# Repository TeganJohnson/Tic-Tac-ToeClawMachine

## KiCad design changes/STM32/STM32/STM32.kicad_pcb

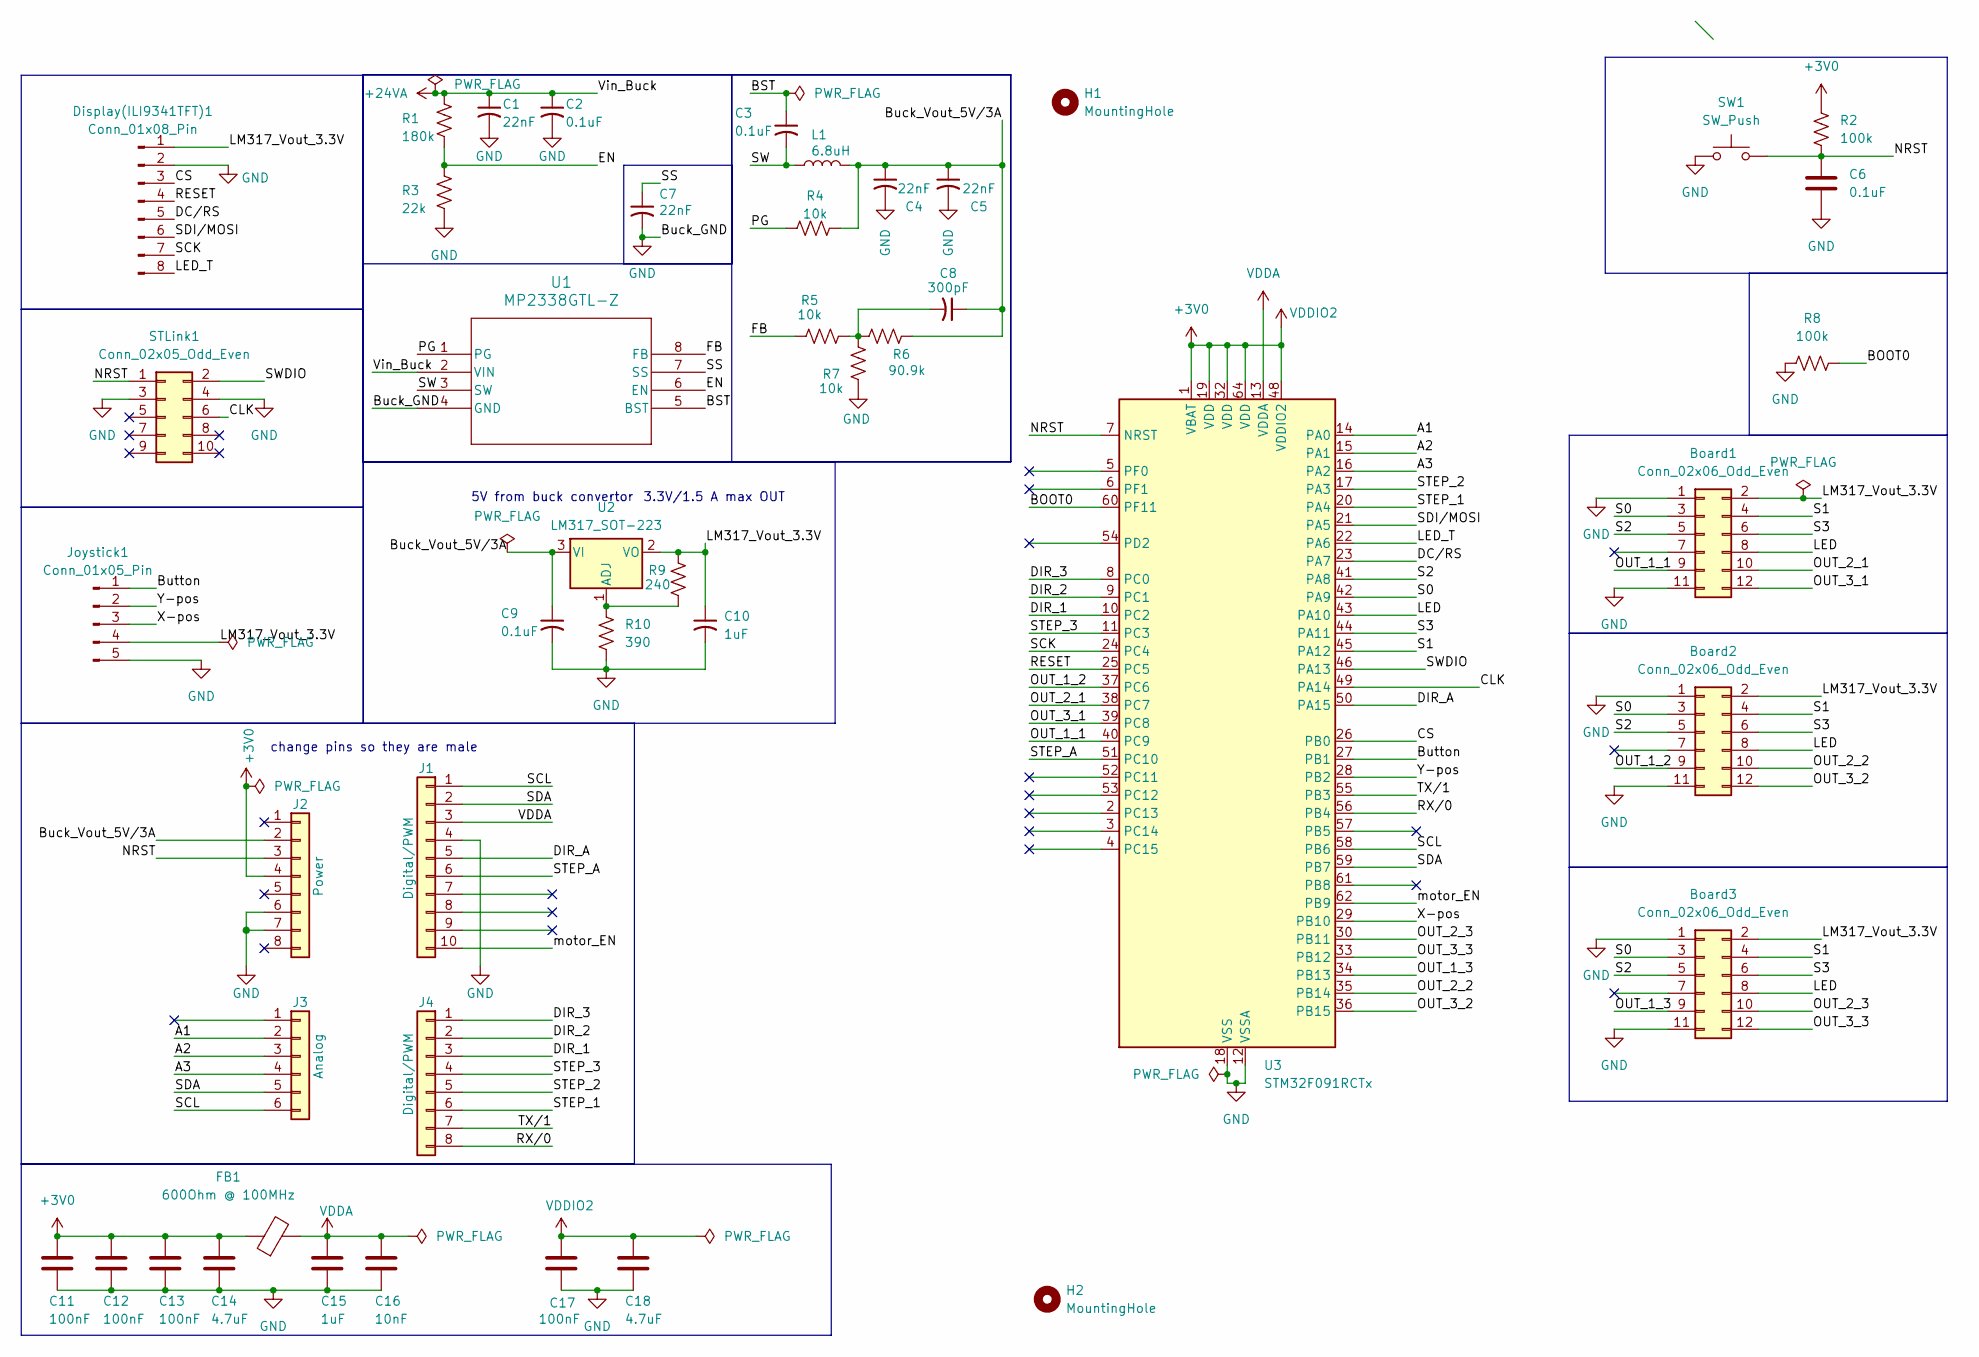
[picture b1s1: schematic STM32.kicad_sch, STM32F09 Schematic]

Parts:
Board1, Board2, Board3: Conn_02x06_Odd_Even; IDC-Header_2x06_P2.54mm_Latch6.5mm_Vertical
C1, C4, C5, C7: 22nF; C_0805_2012Metric
C2, C3, C9: 0.1uF; C_0805_2012Metric
C6: 0.1uF; C_0603_1608Metric
C8: 300pF; C_0805_2012Metric
C10: 1uF; C_0805_2012Metric
C11, C12, C13, C17: 100nF; C_0603_1608Metric
C14, C18: 4.7uF; C_0603_1608Metric
C15: 1uF; C_0603_1608Metric
C16: 10nF; C_0603_1608Metric
Display(ILI9341TFT)1: Conn_01x08_Pin; PinHeader_1x08_P2.54mm_Vertical
FB1: 600Ohm @ 100MHz; R_0603_1608Metric
H1, H2: MountingHole; MountingHole_3.2mm_M3
J1: Digital/PWM; PinSocket_1x10_P2.54mm_Vertical
J2: Power; PinSocket_1x08_P2.54mm_Vertical
J3: Analog; PinSocket_1x06_P2.54mm_Vertical
J4: Digital/PWM; PinSocket_1x08_P2.54mm_Vertical
Joystick1: Conn_01x05_Pin; PinHeader_1x05_P2.54mm_Vertical
L1: 6.8uH; L_0805_2012Metric
R1: 180k; R_0805_2012Metric
R2, R8: 100k; R_0603_1608Metric
R3: 22k; R_0805_2012Metric
R4, R5, R7: 10k; R_0805_2012Metric
R6: 90.9k; R_0805_2012Metric
R9: 240; R_0805_2012Metric
R10: 390; R_0805_2012Metric
STLink1: Conn_02x05_Odd_Even; IDC-Header_2x05_P2.54mm_Vertical
SW1: SW_Push; SW_SPST_TL3342
U1: MP2338GTL-Z; SOT583_MP2338_MNP
U2: LM317_SOT-223; SOT-223-3_TabPin2
U3: STM32F091RCTx; LQFP-64_10x10mm_P0.5mm

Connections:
+3V0: C11.1, C12.1, C13.1, C14.1, C17.1, C18.1, FB1.1, J2.4, R2.1, U3.1 (VBAT), U3.19 (VDD), U3.32 (VDD), U3.48 (VDDIO2), U3.64 (VDD)
+24VA: C1.1, C2.1, R1.1, U1.2 (VIN)
/A1: J3.2, U3.14 (PA0)
/A2: J3.3, U3.15 (PA1)
/A3: J3.4, U3.16 (PA2)
/BOOT0: R8.2, U3.60 (PF11)
/BST: C3.1, U1.5 (BST)
/Buck_Vout_5V/3A: C4.1, C5.1, C8.1, C9.1, J2.2, L1.2, R4.1, R6.2, U2.3 (VI)
/Button: Joystick1.1, U3.27 (PB1)
/CLK: STLink1.6, U3.49 (PA14)
/CS: Display(ILI9341TFT)1.3, U3.26 (PB0)
/DC/RS: Display(ILI9341TFT)1.5, U3.23 (PA7)
/DIR_1: J4.3, U3.10 (PC2)
/DIR_2: J4.2, U3.9 (PC1)
/DIR_3: J4.1, U3.8 (PC0)
/DIR_A: J1.5, U3.50 (PA15)
/EN: R1.2, R3.1, U1.6 (EN)
/FB: R5.2, U1.8 (FB)
/LED: Board1.8, Board2.8, Board3.8, U3.43 (PA10)
/LED_T: Display(ILI9341TFT)1.8, U3.22 (PA6)
/LM317_Vout_3.3V: Board1.2, Board2.2, Board3.2, C10.1, Display(ILI9341TFT)1.1, Joystick1.4, R9.1, U2.2 (VO)
/NRST: C6.1, J2.3, R2.2, STLink1.1, SW1.2, U3.7 (NRST)
/OUT_1_1: Board1.9, U3.40 (PC9)
/OUT_1_2: Board2.9, U3.37 (PC6)
/OUT_1_3: Board3.9, U3.34 (PB13)
/OUT_2_1: Board1.10, U3.38 (PC7)
/OUT_2_2: Board2.10, U3.35 (PB14)
/OUT_2_3: Board3.10, U3.30 (PB11)
/OUT_3_1: Board1.12, U3.39 (PC8)
/OUT_3_2: Board2.12, U3.36 (PB15)
/OUT_3_3: Board3.12, U3.33 (PB12)
/PG: R4.2, U1.1 (PG)
/RESET: Display(ILI9341TFT)1.4, U3.25 (PC5)
/RX/0: J4.8, U3.56 (PB4)
/S0: Board1.3, Board2.3, Board3.3, U3.42 (PA9)
/S1: Board1.4, Board2.4, Board3.4, U3.45 (PA12)
/S2: Board1.5, Board2.5, Board3.5, U3.41 (PA8)
/S3: Board1.6, Board2.6, Board3.6, U3.44 (PA11)
/SCK: Display(ILI9341TFT)1.7, U3.24 (PC4)
/SCL: J1.1, J3.6, U3.58 (PB6)
/SDA: J1.2, J3.5, U3.59 (PB7)
/SDI/MOSI: Display(ILI9341TFT)1.6, U3.21 (PA5)
/SS: C7.1, U1.7 (SS)
/STEP_1: J4.6, U3.20 (PA4)
/STEP_2: J4.5, U3.17 (PA3)
/STEP_3: J4.4, U3.11 (PC3)
/STEP_A: J1.6, U3.51 (PC10)
/SW: C3.2, L1.1, U1.3 (SW)
/SWDIO: STLink1.2, U3.46 (PA13)
/TX/1: J4.7, U3.55 (PB3)
/X-pos: Joystick1.3, U3.29 (PB10)
/Y-pos: Joystick1.2, U3.28 (PB2)
/motor_EN: J1.10, U3.62 (PB9)
GND: Board1.1, Board1.11, Board2.1, Board2.11, Board3.1, Board3.11, C1.2, C2.2, C4.2, C5.2, C6.2, C7.2, C9.2, C10.2, C11.2, C12.2, C13.2, C14.2, C15.2, C16.2, C17.2, C18.2, Display(ILI9341TFT)1.2, J1.4, J2.6, J2.7, Joystick1.5, R3.2, R7.2, R8.1, R10.2, STLink1.3, STLink1.4, SW1.1, U1.4 (GND), U3.12 (VSSA), U3.18 (VSS), U3.31 (VSS), U3.47 (VSS), U3.63 (VSS)
unnamed: C8.2, R5.1, R6.1, R7.1
unnamed: R9.2, R10.1, U2.1 (ADJ)
VDDA: C15.1, C16.1, FB1.2, J1.3, U3.13 (VDDA)

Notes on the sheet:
3.3V/1.5 A max OUT
change pins so they are male
5V from buck convertor

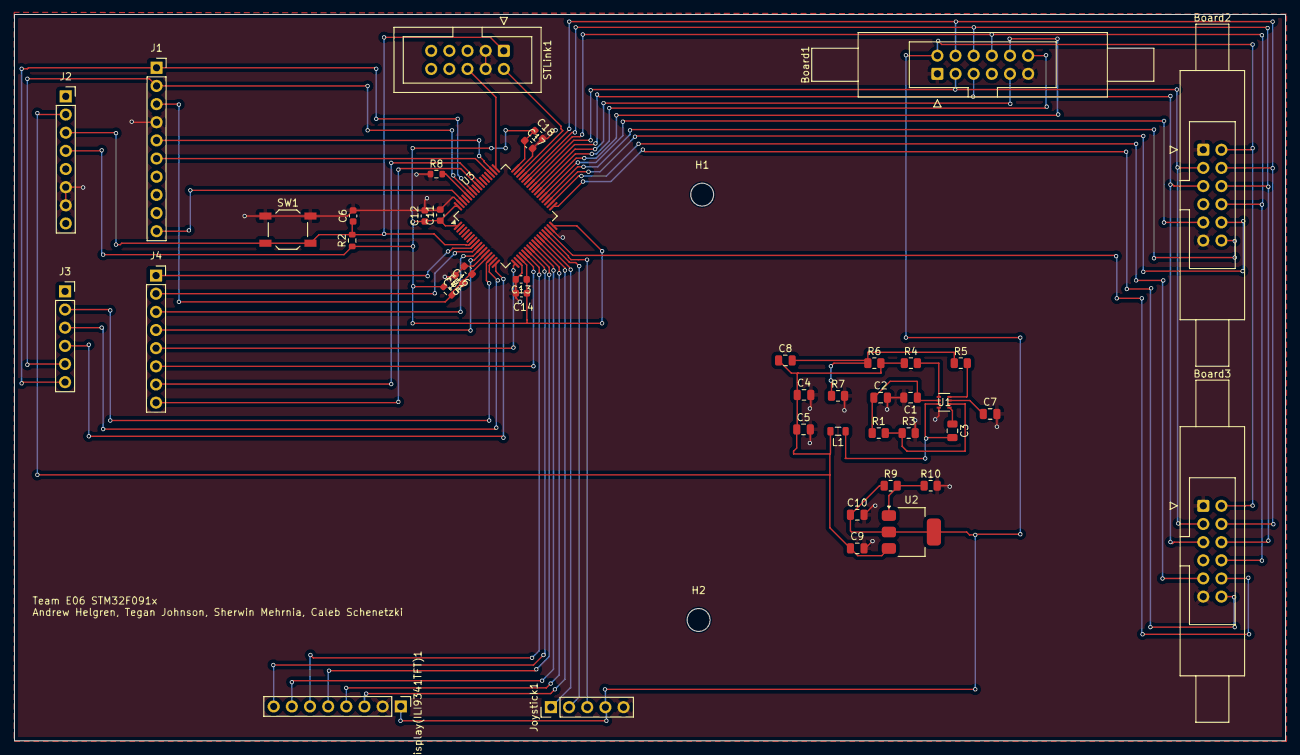
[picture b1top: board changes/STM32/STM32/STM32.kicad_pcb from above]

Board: 2 copper layers, 177.8 x 101.6 mm, 46 parts (0 on the bottom side), 57 nets.

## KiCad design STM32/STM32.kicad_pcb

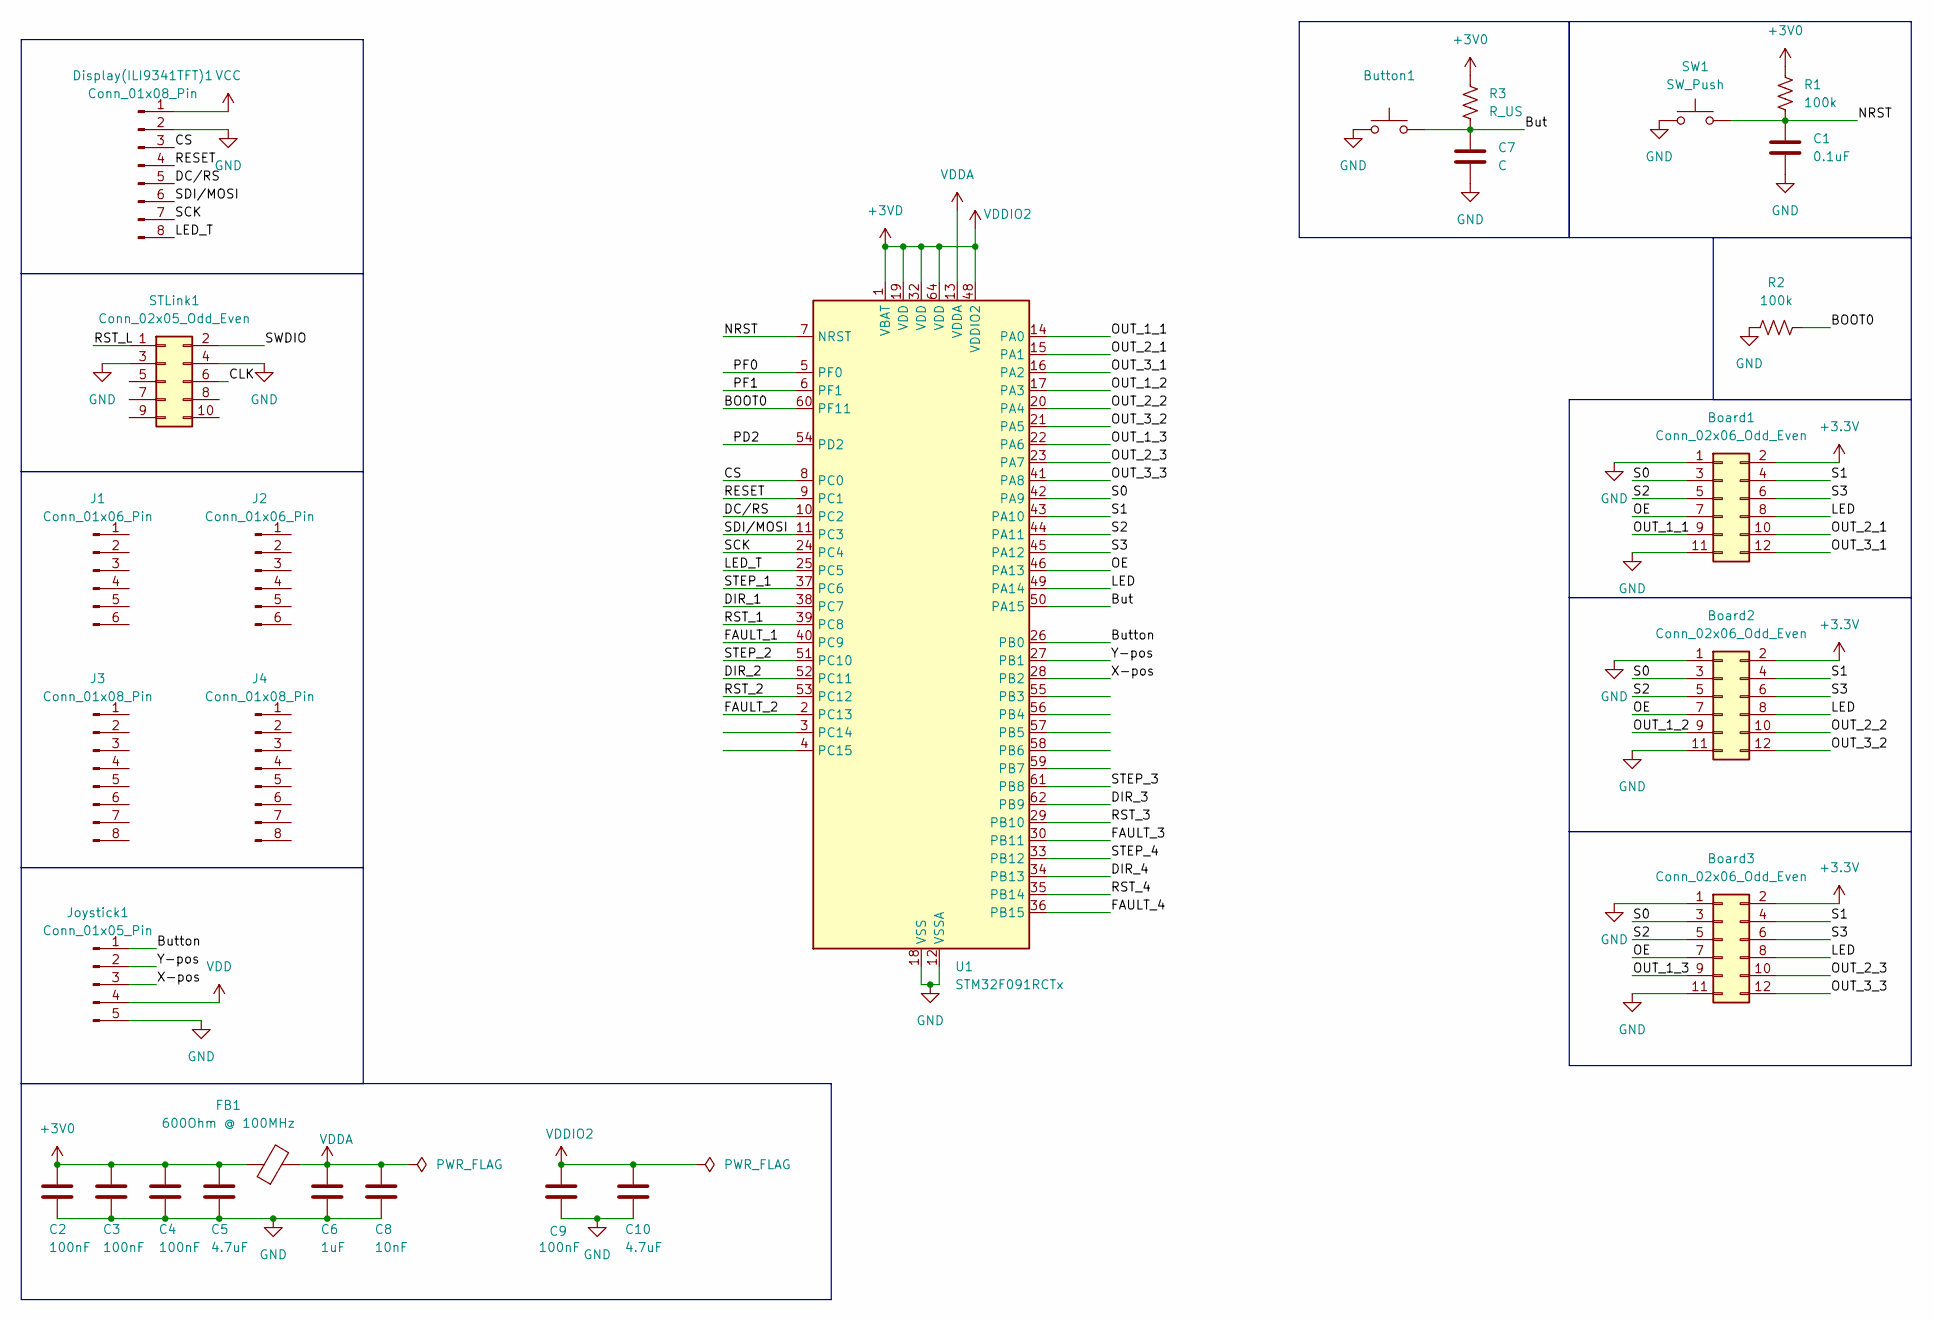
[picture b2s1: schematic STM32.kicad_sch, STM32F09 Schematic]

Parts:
Board1, Board2, Board3: Conn_02x06_Odd_Even; PinHeader_2x06_P1.00mm_Vertical
Button1: SW_SPST_TL3342
C1: 0.1uF; C_0603_1608Metric
C2, C3, C4, C9: 100nF; C_0603_1608Metric
C5, C10: 4.7uF; C_0603_1608Metric
C6: 1uF; C_0603_1608Metric
C7: C; C_0603_1608Metric
C8: 10nF; C_0603_1608Metric
Display(ILI9341TFT)1: Conn_01x08_Pin; PinHeader_1x08_P1.00mm_Vertical
FB1: 600Ohm @ 100MHz; R_0603_1608Metric
J1, J2: Conn_01x06_Pin; PinHeader_1x06_P1.00mm_Vertical
J3, J4: Conn_01x08_Pin; PinHeader_1x08_P1.00mm_Vertical
Joystick1: Conn_01x05_Pin; PinHeader_1x05_P1.00mm_Vertical
R1, R2: 100k; R_0603_1608Metric
R3: R_US; R_0603_1608Metric
STLink1: Conn_02x05_Odd_Even; PinHeader_2x05_P1.00mm_Vertical
SW1: SW_Push; SW_SPST_TL3342
U1: STM32F091RCTx; LQFP-64_10x10mm_P0.5mm

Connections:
+3.3V: Board1.2, Board2.2, Board3.2
+3V0: C2.1, C3.1, C4.1, C5.1, FB1.1, R1.1, R3.1
+3VD: C9.1, C10.1, U1.1 (VBAT), U1.19 (VDD), U1.32 (VDD), U1.48 (VDDIO2), U1.64 (VDD)
/BOOT0: R2.2, U1.60 (PF11)
/But: Button1.2, C7.1, R3.2, U1.50 (PA15)
/Button: Joystick1.1, U1.26 (PB0)
/CLK: STLink1.6
/CS: Display(ILI9341TFT)1.3, U1.8 (PC0)
/DC/RS: Display(ILI9341TFT)1.5, U1.10 (PC2)
/DIR_1: U1.38 (PC7)
/DIR_2: U1.52 (PC11)
/DIR_3: U1.62 (PB9)
/DIR_4: U1.34 (PB13)
/FAULT_1: U1.40 (PC9)
/FAULT_2: U1.2 (PC13)
/FAULT_3: U1.30 (PB11)
/FAULT_4: U1.36 (PB15)
/LED: Board1.8, Board2.8, Board3.8, U1.49 (PA14)
/LED_T: Display(ILI9341TFT)1.8, U1.25 (PC5)
/NRST: C1.1, R1.2, SW1.2, U1.7 (NRST)
/OE: Board1.7, Board2.7, Board3.7, U1.46 (PA13)
/OUT_1_1: Board1.9, U1.14 (PA0)
/OUT_1_2: Board2.9, U1.17 (PA3)
/OUT_1_3: Board3.9, U1.22 (PA6)
/OUT_2_1: Board1.10, U1.15 (PA1)
/OUT_2_2: Board2.10, U1.20 (PA4)
/OUT_2_3: Board3.10, U1.23 (PA7)
/OUT_3_1: Board1.12, U1.16 (PA2)
/OUT_3_2: Board2.12, U1.21 (PA5)
/OUT_3_3: Board3.12, U1.41 (PA8)
/PD2: U1.54 (PD2)
/PF0: U1.5 (PF0)
/PF1: U1.6 (PF1)
/RESET: Display(ILI9341TFT)1.4, U1.9 (PC1)
/RST_1: U1.39 (PC8)
/RST_2: U1.53 (PC12)
/RST_3: U1.29 (PB10)
/RST_4: U1.35 (PB14)
/RST_L: STLink1.1
/S0: Board1.3, Board2.3, Board3.3, U1.42 (PA9)
/S1: Board1.4, Board2.4, Board3.4, U1.43 (PA10)
/S2: Board1.5, Board2.5, Board3.5, U1.44 (PA11)
/S3: Board1.6, Board2.6, Board3.6, U1.45 (PA12)
/SCK: Display(ILI9341TFT)1.7, U1.24 (PC4)
/SDI/MOSI: Display(ILI9341TFT)1.6, U1.11 (PC3)
/STEP_1: U1.37 (PC6)
/STEP_2: U1.51 (PC10)
/STEP_3: U1.61 (PB8)
/STEP_4: U1.33 (PB12)
/SWDIO: STLink1.2
/X-pos: Joystick1.3, U1.28 (PB2)
/Y-pos: Joystick1.2, U1.27 (PB1)
GND: Board1.1, Board1.11, Board2.1, Board2.11, Board3.1, Board3.11, Button1.1, C1.2, C2.2, C3.2, C4.2, C5.2, C6.2, C7.2, C8.2, C9.2, C10.2, Display(ILI9341TFT)1.2, Joystick1.5, R2.1, STLink1.3, STLink1.4, SW1.1, U1.12 (VSSA), U1.18 (VSS), U1.31 (VSS), U1.47 (VSS), U1.63 (VSS)
VCC: Display(ILI9341TFT)1.1
VDD: Joystick1.4
VDDA: C6.1, C8.1, FB1.2, U1.13 (VDDA)

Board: 2 copper layers, 27 parts (0 on the bottom side), 32 nets, no tracks yet.

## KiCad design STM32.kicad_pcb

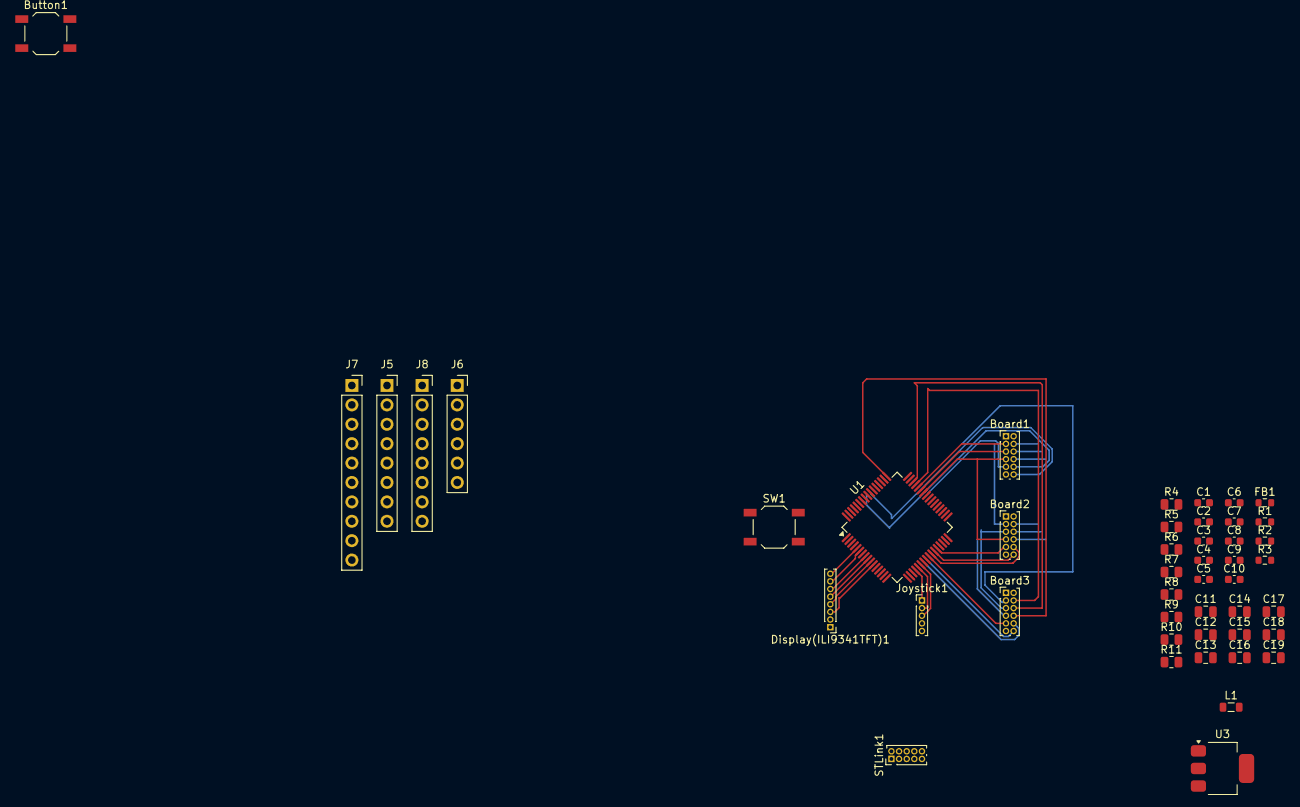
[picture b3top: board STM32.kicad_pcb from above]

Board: 2 copper layers, 46 parts (0 on the bottom side), 42 nets.

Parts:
Board1, Board2, Board3: Conn_02x06_Odd_Even; PinHeader_2x06_P1.00mm_Vertical
Button1: SW_SPST_TL3342
C1: 0.1uF; C_0603_1608Metric
C2, C3, C4, C9: 100nF; C_0603_1608Metric
C5, C10: 4.7uF; C_0603_1608Metric
C6: 1uF; C_0603_1608Metric
C7: C; C_0603_1608Metric
C8: 10nF; C_0603_1608Metric
C11, C14, C15, C16: 22nF; C_0805_2012Metric
C12, C13, C18: 0.1uF; C_0805_2012Metric
C17: 300pF; C_0805_2012Metric
C19: 1uF; C_0805_2012Metric
Display(ILI9341TFT)1: Conn_01x08_Pin; PinHeader_1x08_P1.00mm_Vertical
FB1: 600Ohm @ 100MHz; R_0603_1608Metric
J5: Power; PinSocket_1x08_P2.54mm_Vertical
J6: Analog; PinSocket_1x06_P2.54mm_Vertical
J7: Digital/PWM; PinSocket_1x10_P2.54mm_Vertical
J8: Digital/PWM; PinSocket_1x08_P2.54mm_Vertical
Joystick1: Conn_01x05_Pin; PinHeader_1x05_P1.00mm_Vertical
L1: 6.8uH; L_0805_2012Metric
R1, R2: 100k; R_0603_1608Metric
R3: R_US; R_0603_1608Metric
R4: 180k; R_0805_2012Metric
R5: 22k; R_0805_2012Metric
R6, R7, R9: 10k; R_0805_2012Metric
R8: 90.9k; R_0805_2012Metric
R10: 240; R_0805_2012Metric
R11: 390; R_0805_2012Metric
STLink1: Conn_02x05_Odd_Even; PinHeader_2x05_P1.00mm_Vertical
SW1: SW_Push; SW_SPST_TL3342
U1: STM32F091RCTx; LQFP-64_10x10mm_P0.5mm
U3: LM317_SOT-223; SOT-223-3_TabPin2

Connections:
+3.3V: Board1.2, Board2.2, Board3.2
+3V0: C2.1, C3.1, C4.1, C5.1, C9.1, C10.1, FB1.1, R1.1, R3.1, U1.1 (VBAT), U1.19 (VDD), U1.32 (VDD), U1.48 (VDDIO2), U1.64 (VDD)
+5V: C18.1, J5.5, U3.3 (VI)
+24VA: C11.1, C12.1, R4.1
/BOOT0: R2.2, U1.60 (PF11)
/Buck_Vout_5V/3A: C14.1, C15.1, C17.1, L1.2, R6.1, R8.2
/But: Button1.2, C7.1, R3.2, U1.50 (PA15)
/Button: Joystick1.1, U1.20 (PA4)
/CS: Display(ILI9341TFT)1.3, U1.11 (PC3)
/DC/RS: Display(ILI9341TFT)1.5, U1.9 (PC1)
/EN: R4.2, R5.1
/LED: Board1.8, Board2.8, Board3.8, U1.49 (PA14)
/LED_T: Display(ILI9341TFT)1.8, U1.5 (PF0)
/LM317_Vout_3.3V: C19.1, R10.1, U3.2 (VO)
/NRST: C1.1, R1.2, SW1.2, U1.7 (NRST)
/OE: Board1.7, Board2.7, Board3.7, U1.42 (PA9)
/OUT_1_1: Board1.9, U1.41 (PA8)
/OUT_1_2: Board2.9, U1.28 (PB2)
/OUT_1_3: Board3.9, U1.25 (PC5)
/OUT_2_1: Board1.10, U1.56 (PB4)
/OUT_2_2: Board2.10, U1.26 (PB0)
/OUT_2_3: Board3.10, U1.23 (PA7)
/OUT_3_1: Board1.12, U1.55 (PB3)
/OUT_3_2: Board2.12, U1.27 (PB1)
/OUT_3_3: Board3.12, U1.24 (PC4)
/RESET: Display(ILI9341TFT)1.4, U1.10 (PC2)
/S0: Board1.3, Board2.3, Board3.3, U1.44 (PA11)
/S1: Board1.4, Board2.4, Board3.4, U1.45 (PA12)
/S2: Board1.5, Board2.5, Board3.5, U1.43 (PA10)
/S3: Board1.6, Board2.6, Board3.6, U1.46 (PA13)
/SCK: Display(ILI9341TFT)1.7, U1.6 (PF1)
/SCL/A5: J6.6, J7.1
/SDA/A4: J6.5, J7.2
/SDI/MOSI: Display(ILI9341TFT)1.6, U1.8 (PC0)
/SW: C13.2, L1.1
/X-pos: Joystick1.3, U1.22 (PA6)
/Y-pos: Joystick1.2, U1.21 (PA5)
GND: Board1.1, Board1.11, Board2.1, Board2.11, Board3.1, Board3.11, Button1.1, C1.2, C2.2, C3.2, C4.2, C5.2, C6.2, C7.2, C8.2, C9.2, C10.2, C11.2, C12.2, C14.2, C15.2, C16.2, C18.2, C19.2, Display(ILI9341TFT)1.2, J5.6, J5.7, J7.4, Joystick1.5, R2.1, R5.2, R9.2, R11.2, STLink1.3, STLink1.4, SW1.1, U1.12 (VSSA), U1.18 (VSS), U1.31 (VSS), U1.47 (VSS), U1.63 (VSS)
unnamed: C17.2, R7.1, R8.1, R9.1
unnamed: R10.2, R11.1, U3.1 (ADJ)
VCC: Display(ILI9341TFT)1.1, J5.8
VDDA: C6.1, C8.1, FB1.2, U1.13 (VDDA)

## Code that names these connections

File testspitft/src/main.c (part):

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#include "display.h"

// LCD Pin Connections (STM32F091RC)
// PB0  -> Chip Select (CS)
// PC5  -> Reset (RST)
// PA7  -> Data/Command Select (DC/RS)
// PA6  -> Backlight (LED_T)
// PC4  -> SPI1_SCK  (AF0)
// PA5  -> SPI1_MOSI (AF0)

#define LCD_CS_GPIO GPIOB
#define LCD_CS_PIN 0
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#define JOY_GPIO GPIOB
#define JOY_BTN_PIN 1

#define JOY_X_CHANNEL ADC_CHSELR_CHSEL0 // PB10 -> ADC channel 11 PA0 - 0
#define JOY_Y_CHANNEL ADC_CHSELR_CHSEL1 // PB2  -> ADC channel 12 (if wired, else verify) PA1 - 1

#define X_LIMIT_GPIO GPIOB
#define X_LIMIT_PIN 4
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    // Enable GPIOA, GPIOB, GPIOC clocks
    RCC->AHBENR |= RCC_AHBENR_GPIOAEN | RCC_AHBENR_GPIOBEN | RCC_AHBENR_GPIOCEN;

    // PB0 (CS) output, start high (deselected)
    GPIOB->MODER &= ~(3 << (0 * 2));
    GPIOB->MODER |= (1 << (0 * 2));
    GPIOB->BSRR = (1 << 0);

    // PC5 (RST) output, start high
    GPIOC->MODER &= ~(3 << (5 * 2));
    GPIOC->MODER |= (1 << (5 * 2));
    GPIOC->BSRR = (1 << 5);

    // PA7 (DC) output now pc4
    GPIOC->MODER &= ~(3 << (4 * 2));
    GPIOC->MODER |= (1 << (4 * 2));

    // PA6 (Backlight) output, start high (on)
    GPIOA->MODER &= ~(3 << (6 * 2));
    GPIOA->MODER |= (1 << (6 * 2));
    GPIOA->BSRR = (1 << 6);

    // PC4 -> SPI1_SCK AF0 now pa5
    GPIOA->MODER &= ~(3 << (5 * 2));
    GPIOA->MODER |= (2 << (5 * 2));
    GPIOA->AFR[0] &= ~(0xF << (5 * 4));

    // PA5 -> SPI1_MOSI AF0 mpw pa7
    GPIOA->MODER &= ~(3 << (7 * 2));
    GPIOA->MODER |= (2 << (7 * 2));
    GPIOA->AFR[0] &= ~(0xF << (7 * 4));

    // PB10 (X-pos) analog, ADC ch11 not PA0
    GPIOA->MODER |= (3 << (0 * 2));
    GPIOA->PUPDR &= ~(3 << (0 * 2));

    // PB2 (Y-pos) analog, ADC ch12 now PA1
    GPIOA->MODER |= (3 << (1 * 2));
    GPIOA->PUPDR &= ~(3 << (1 * 2));

    // PB1 (Button) input with pull-up
    GPIOB->MODER &= ~(3 << (JOY_BTN_PIN * 2));
    GPIOB->PUPDR &= ~(3 << (JOY_BTN_PIN * 2));
    GPIOB->PUPDR |= (1 << (JOY_BTN_PIN * 2));

    // --- Shared TCS control pins: PA8, PA9, PA10, PA11, PA12 as outputs ---
    GPIOA->MODER &= ~((3 << (8 * 2)) |
                      (3 << (9 * 2)) |
                      (3 << (10 * 2)) |
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
    // --- 9 TCS output pins as digital inputs ---

    // PC6, PC7, PC8, PC9
    GPIOC->MODER &= ~((3 << (6 * 2)) |
                      (3 << (7 * 2)) |
                      (3 << (8 * 2)) |
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                      (3 << (8 * 2)) |
                      (3 << (9 * 2)));

    // PB11, PB12, PB13, PB14, PB15
    GPIOB->MODER &= ~((3 << (11 * 2)) |
                      (3 << (12 * 2)) |
                      (3 << (13 * 2)) |
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
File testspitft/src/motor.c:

#include "motor.h"
 
// -----------------------------------------------------------------------------
// External timing functions from main.c
// ----------------------------------------------------------------------------
extern uint32_t millis(void);
extern void delay_ms(uint32_t ms);

// -----------------------------------------------------------------------------
// Number of Steps to Lower/Raise to/from the Play Area
// -----------------------------------------------------------------------------
#define LOWER_STEPS 1000
#define RAISE_STEPS 1000

// -----------------------------------------------------------------------------
// Number of Steps to Close/Open the Claw
// -----------------------------------------------------------------------------
#define CLOSE_STEPS 10
#define OPEN_STEPS 10 

// -----------------------------------------------------------------------------
// Number of Steps to Set the Drop Height
// -----------------------------------------------------------------------------
#define DROP_STEPS 0
#define DROP_RAISE_STEPS 0

#define X_LIMIT_GPIO GPIOB
#define X_LIMIT_PIN 3

#define Y_LIMIT_GPIO GPIOB
#define Y_LIMIT_PIN 4

// -----------------------------------------------------------------------------
// Microsecond busy-wait
// Assumes 8MHz system clock. Adjust cycle count if clock changes.
// Each loop iteration ~ 4 cycles at 8MHz = 0.5us, so 2 iterations ~ 1us.
// -----------------------------------------------------------------------------
static void delay_us(uint32_t us)
{
    volatile uint32_t cycles = us * 2;
    while (cycles--) __NOP();
}
 
// -----------------------------------------------------------------------------
// Pin mapping — matches confirmed schematic
// -----------------------------------------------------------------------------
//   AXIS_X    STEP=PA4  DIR=PC2
//   AXIS_Y    STEP=PA3  DIR=PC1
//   AXIS_Z    STEP=PC3  DIR=PC0
//   AXIS_CLAW STEP=PC10 DIR=PA15
//
// Shared enable: PB9 (active LOW on DRV8825)
// -----------------------------------------------------------------------------

#define MOTOR_EN_PORT   GPIOB
#define MOTOR_EN_PIN    9
 
static const motor_pins_t motor_pins[AXIS_COUNT] = {
    [AXIS_X]    = { GPIOA, 4,  GPIOC, 2  },
    [AXIS_Y]    = { GPIOA, 3,  GPIOC, 1  },
    [AXIS_Z]    = { GPIOC, 3,  GPIOC, 0  },
    [AXIS_CLAW] = { GPIOC, 10, GPIOA, 15 },
};

// -----------------------------------------------------------------------------
//A helper function for Motor_Init
// -----------------------------------------------------------------------------
void gpio_pullup(GPIO_TypeDef *port, uint8_t pin) {
    port->MODER &= ~(3 << (pin * 2));
    port->PUPDR &= ~(3 << (pin * 2));
    port->PUPDR |= (1 << (pin * 2));
}

 
// -----------------------------------------------------------------------------
// Motor_Init
// Configures all STEP, DIR, and EN pins as outputs.
// Call after GPIO clocks have been enabled in GPIO_Init().
// -----------------------------------------------------------------------------
void Motor_Init(void)
{

    gpio_pullup(X_LIMIT_GPIO, X_LIMIT_PIN);
    gpio_pullup(Y_LIMIT_GPIO, Y_LIMIT_PIN);

    // Enable pin — PB9 output, start HIGH (disabled)
    MOTOR_EN_PORT->MODER &= ~(3 << (MOTOR_EN_PIN * 2));
    MOTOR_EN_PORT->MODER |=  (1 << (MOTOR_EN_PIN * 2));
    MOTOR_EN_PORT->BSRR   =  (1 << MOTOR_EN_PIN);      // HIGH = disabled
 
    for (uint8_t i = 0; i < AXIS_COUNT; i++) {
        const motor_pins_t *p = &motor_pins[i];
 
        // STEP pin — output, start low
        p->step_port->MODER &= ~(3 << (p->step_pin * 2));
        p->step_port->MODER |=  (1 << (p->step_pin * 2));
        p->step_port->BRR    =  (1 << p->step_pin);
 
        // DIR pin — output, start low
        p->dir_port->MODER &= ~(3 << (p->dir_pin * 2));
        p->dir_port->MODER |=  (1 << (p->dir_pin * 2));
        p->dir_port->BRR    =  (1 << p->dir_pin);
    }
}
 
// -----------------------------------------------------------------------------
// Motor_Enable / Motor_Disable
// DRV8825 EN is active LOW — pull low to enable, high to disable.
// Disable when not moving to reduce heat and current draw.
// -----------------------------------------------------------------------------
void Motor_Enable(void)
{
    MOTOR_EN_PORT->BRR  = (1 << MOTOR_EN_PIN);   // LOW = enabled
}
 
void Motor_Disable(void)
{
    MOTOR_EN_PORT->BSRR = (1 << MOTOR_EN_PIN);   // HIGH = disabled
}
 
//Motor_Step2, currently is blocking.
//takes up to 2 axis and moves them the given number of steps.
//unused axis should be input as 2
void Motor_Step2(axis_t axis1, axis_t axis2, motor_dir_t dir, uint32_t steps)
{
    if (axis1 >= AXIS_COUNT || axis2 >= AXIS_COUNT || steps == 0) return;
 
    const motor_pins_t *p1 = &motor_pins[axis1];

    const motor_pins_t *p2 = &motor_pins[axis2];

    if (dir == DIR_FORWARD) {
    p2->dir_port->BSRR = (1 << p2->dir_pin);   // HIGH
    } else {
    p2->dir_port->BRR  = (1 << p2->dir_pin);   // LOW
    }
        
    if (dir == DIR_FORWARD) {
    p1->dir_port->BSRR = (1 << p1->dir_pin);   // HIGH
    } else {
    p1->dir_port->BRR  = (1 << p1->dir_pin);   // LOW
    }

    //delay for DRV8825 setup
    delay_us(2);
 
    for (uint32_t i = 0; i < steps; i++) {
        // Pulse STEP high
        p1->step_port->BSRR = (1 << p1->step_pin);
        p2->step_port->BSRR = (1 << p2->step_pin);
        delay_us(MOTOR_PULSE_US);
 
        // Pulse STEP low
        p1->step_port->BRR  = (1 << p1->step_pin);

        p2->step_port->BRR  = (1 << p2->step_pin);
        delay_us(MOTOR_STEP_DELAY_US);
    }
    }


void Motor_Step(axis_t axis1, motor_dir_t dir, uint32_t steps)
{
    if (axis1 >= AXIS_COUNT || steps == 0) return;
 
    const motor_pins_t *p = &motor_pins[axis1];
 
    //set direction
    if (dir == DIR_FORWARD) {
        p->dir_port->BSRR = (1 << p->dir_pin);   // HIGH
    } else {
        p->dir_port->BRR  = (1 << p->dir_pin);   // LOW
    }

    //delay for DRV8825 setup
    delay_us(2);
 
    for (uint32_t i = 0; i < steps; i++) {
        // Pulse STEP high
        p->step_port->BSRR = (1 << p->step_pin);
        delay_us(MOTOR_PULSE_US);
 
        // Pulse STEP low
        p->step_port->BRR  = (1 << p->step_pin);
        delay_us(MOTOR_STEP_DELAY_US);
    }
}

void Claw_Grab_Token(void) {
    Motor_MoveZ(DIR_FORWARD, LOWER_STEPS);
    delay_ms(1000);
    Motor_MoveClaw(DIR_FORWARD, CLOSE_STEPS);
    Motor_MoveZ(DIR_BACKWARD, RAISE_STEPS);
}

void Claw_Drop_Token(void) {
    if (DROP_STEPS != 0) {
        Motor_MoveZ(DIR_FORWARD, DROP_STEPS);
    }

    Motor_MoveClaw(DIR_BACKWARD, OPEN_STEPS);

    if (DROP_STEPS != 0) {
        Motor_MoveZ(DIR_FORWARD, DROP_RAISE_STEPS);
    }
}
 
//wrappers
void Motor_MoveX(motor_dir_t dir, uint32_t steps)
{
    Motor_Step(AXIS_X, dir, steps);
}
 
void Motor_MoveY(motor_dir_t dir, uint32_t steps)
{
    Motor_Step(AXIS_Y, dir, steps);
}
 
void Motor_MoveZ(motor_dir_t dir, uint32_t steps)
{
    Motor_Step(AXIS_Z, dir, steps);
}
 
void Motor_MoveClaw(motor_dir_t dir, uint32_t steps)
{
    Motor_Step(AXIS_CLAW, dir, steps);
}
 
void Motor_MoveXZ(motor_dir_t dir, uint32_t steps) {
    Motor_Step2(AXIS_Z, AXIS_X, dir, steps);
}

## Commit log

2026-01-17 Journal 1 Sem 2
2026-02-02 STM32
2026-02-05 STM schematic
2026-02-13 Add files via upload
    adjusted schematic
2026-02-17 kicad power and cncshieldconnectors
2026-02-17 newfilestoreview
2026-02-17 mp2338
2026-03-06 Basic project reformatting
2026-03-28 Week 11 Updates - Actual Pin Mapping and Begininning Motor Control
2026-04-02 Modified for breadboard test, but USB Driver Issues
2026-04-03 WorkingLCD with switched pins
2026-04-03 Working LCD and Joystick
2026-04-03 Very bare bones Joystick and Motor Integration. No TFT.
2026-04-03 Crappy interrupt based timer w/ Joystick+Motors
2026-04-14 Limit Switch Addition
2026-04-14 Working on State Logic
2026-04-14 Current Game State
2026-04-15 Build-able Game Logic
2026-04-16 More Refined Game Logic -Display Timer Updates Shortened
2026-04-17 PCB Motor Testing 4/17
2026-04-17 Checkoffs for 4/17 FINAL
2026-04-20 random changes
